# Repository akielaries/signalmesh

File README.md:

# signalmesh
*signalmesh* is a hybrid analog/digital synthesizer. For now it is a mess of reworked PCBs, perf/breadboards, and wires on my desk.

CAD work going on here right now: https://github.com/akielaries/signalmesh_CAD/

# Details
Don't forget to initialize submodules. ChibiOS is the RTOS used in this project on an STM32H7. I'm mostly building around an H755, 
occasionally the H753 but the H745/743 will probably work as well. AFAIK the only difference is the additional ARM M4 core and some
crypo acceleration stuff.

```
git submodule init
git submodule update
```

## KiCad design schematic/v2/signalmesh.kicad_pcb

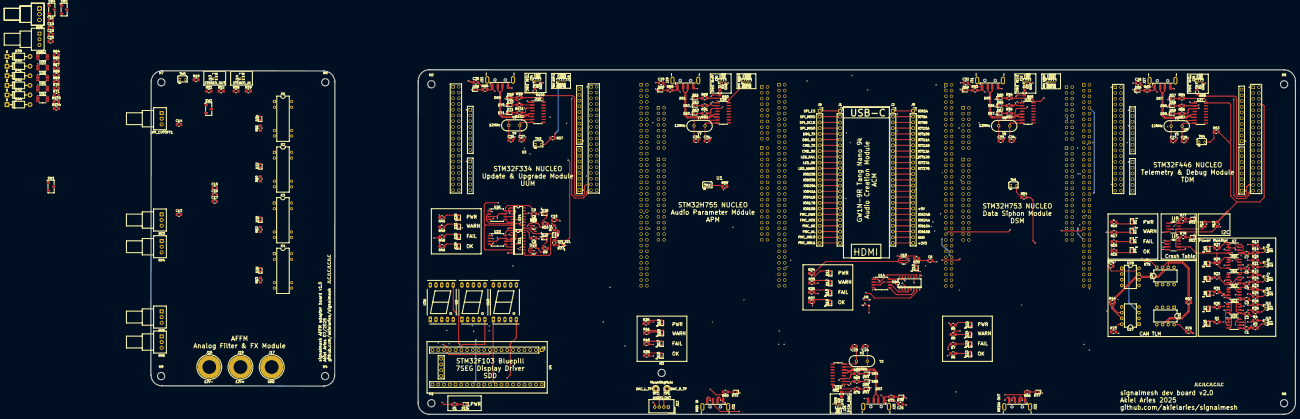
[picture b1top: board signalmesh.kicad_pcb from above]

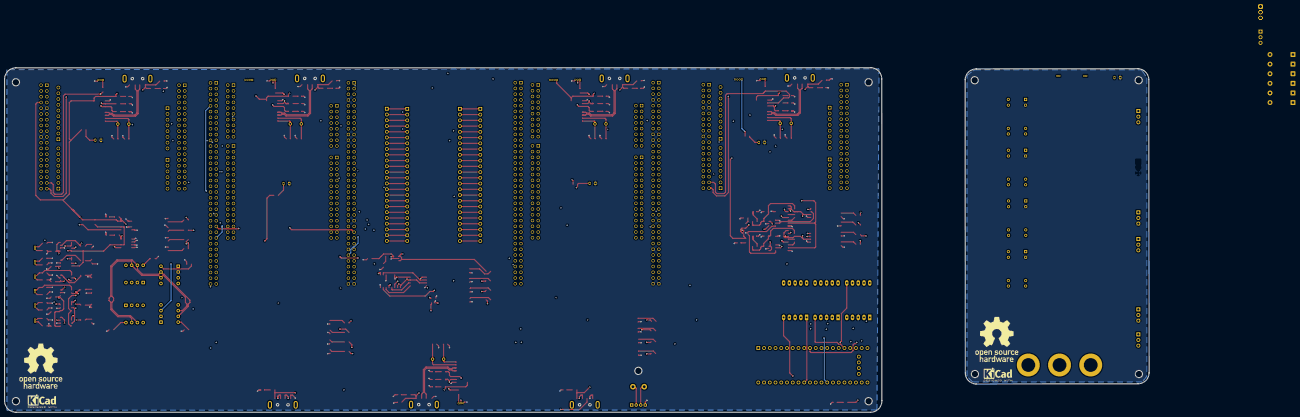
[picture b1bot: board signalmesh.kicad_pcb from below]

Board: 4 copper layers, 506.0 x 152.3 mm, 315 parts (4 on the bottom side), 286 nets.

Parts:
C1, C2, C3, C4, C5, C7, C10, C13, C14, C15, C16, C17: 0.1uf; C_0805_2012Metric
C6, C8, C9: 10uf; C_0805_2012Metric
C11, C20: 1uf; C_0805_2012Metric
C18, C19: 10nf; C_0805_2012Metric
C23, C24, C25, C26, C27, C28, C29, C30, C31, C32, C33, C34, C35, C36, C37: 22pf; C_0805_2012Metric
D1, D12, D16, D22, D29: LED_OK; LED_0603_1608Metric
D2, D13, D17, D23, D30: LED_FAIL; LED_0603_1608Metric
D3, D14, D18, D24, D31: LED_WARN; LED_0603_1608Metric
D4, D5, D6, D7, D8, D9, D10, D11, D15, D19, D20, D21, D25, D26, D28, D32, D37, D38, D51, D52, D53, D56, D57, D60, D61, D64, D65, D68, D69: LED_PWR; LED_0603_1608Metric
D27: SPI_SEL; LED_0603_1608Metric
D33: LPF_ON; LED_0603_1608Metric
D34: HPF_ON; LED_0603_1608Metric
D35: BPF_ON; LED_0603_1608Metric
D36: BSF_ON; LED_0603_1608Metric
D39, D40, D41, D42, D43, D44: 1N4001; D_DO-41_SOD81_P10.16mm_Horizontal
D54, D59, D63, D67, D71: RXD; LED_0603_1608Metric
D55, D58, D62, D66, D70: TXD; LED_0603_1608Metric
H1, H2, H3, H4, H5, H6, H7, H8, H9: MountingHole; MountingHole_3.2mm_M3
J1, J2, J8, J9: FPGA I/O; PinSocket_1x24_P2.54mm_Vertical
J3, J4, J18: LCD_display; PinHeader_1x04_P1.00mm_Horizontal
J5, J6, J7, J10, J11, J15: INA219_CONFIG; PinHeader_1x02_P1.00mm_Horizontal
J12: AUDIO_OUT; NS-Tech_Grove_1x04_P2mm_Vertical
J13: STEREO_OUT; PinHeader_1x02_P1.00mm_Vertical
J14: STEREO_IN; PinHeader_1x02_P1.00mm_Vertical
J16: 12V-; Banana_Jack_1Pin
J17: GND; Banana_Jack_1Pin
J19: 12V+; Banana_Jack_1Pin
J21, J22, J25, J27, J29, J31, J33: USB_A; USB_A_CNCTech_1001-011-01101_Horizontal
J26, J28, J30, J32, J34: UART_DEBUG; PinHeader_1x03_P1.00mm_Horizontal
K1, K2, K3, K4: DIPxx-1Axx-11x; Relay_StandexMeder_DIP_LowProfile
KiCAD_logo: KiCad-Logo2_5mm_SilkScreen
KiCAD_logo#2: KiCad-Logo2_5mm_SilkScreen
LPF_CUTOFF1: 100k; Potentiometer_Alps_RK09Y11_Single_Horizontal
OSHW: OSHW-Logo_19x20mm_SilkScreen
OSHW#2: OSHW-Logo_19x20mm_SilkScreen
R1, R2, R5, R6, R7, R8, R9, R10, R15, R16, R17, R18, R27, R29, R30, R31, R32, R33, R34, R35, R36, R37, R38, R39, R40, R41, R43, R45, R46, R48, R49, R50, R56, R60, R61, R62, R63, R72, R77, R78, R79, R80, R82, R83, R84, R86, R87, R88, R89, R91, R92, R93, R94, R96, R97, R98, R99, R101, R102: 300; R_0805_2012Metric_Pad1.20x1.40mm_HandSolder
R3, R4, R13, R14, R19, R20, R21, R22, R23, R24, R25, R26, R28, R53, R54, R55, R57, R64, R70, R73, R74, R75, R76: 10k; R_0805_2012Metric_Pad1.20x1.40mm_HandSolder
R11, R12: 4.7k; R_0805_2012Metric_Pad1.20x1.40mm_HandSolder
R42: 100; R_0805_2012Metric_Pad1.20x1.40mm_HandSolder
R44, R47: 120; R_0805_2012Metric_Pad1.20x1.40mm_HandSolder
R51, R52: 10K; R_0805_2012Metric_Pad1.20x1.40mm_HandSolder
R58, R59: 1K; R_0805_2012Metric_Pad1.20x1.40mm_HandSolder
R65, R71: 6k8; R_0805_2012Metric_Pad1.20x1.40mm_HandSolder
R67, R103: 200k; R_0805_2012Metric_Pad1.20x1.40mm_HandSolder
R68: 100k; R_0805_2012Metric_Pad1.20x1.40mm_HandSolder
R69: 33k; R_0805_2012Metric_Pad1.20x1.40mm_HandSolder
R81, R85, R90, R95, R100: 1k5; R_0805_2012Metric_Pad1.20x1.40mm_HandSolder
R104: 100K; R_0805_2012Metric_Pad1.20x1.40mm_HandSolder
RV3, RV4, RV5, RV6, RV7, RV8, RV9: 100k; Potentiometer_Alps_RK09Y11_Single_Horizontal
SW1: LPF_FBCK_OUT; Nidec_Copal_CAS-120A
SW2: LPF_IN_SW; Nidec_Copal_CAS-120A
SW4: LPF_OUT_SW; Nidec_Copal_CAS-120A
SW5: LPF_FBCK_IN; Nidec_Copal_CAS-120A
TH1, TH2, TH3, TH4, TH5: 10k; Heraeus_TO-92-2
TP1: DAC_R_TP; TestPoint_THTPad_D2.5mm_Drill1.2mm
TP2: DAC_L_TP; TestPoint_THTPad_D2.5mm_Drill1.2mm
U1, U17: NUCLEO-H753ZI; MODULE_NUCLEO-H753ZI
U2, U18, U36: SM420561N; 7SegmentLED_LTS6760_LTS6780
U3: NUCLEO-F303RE; ST_NUCLEO-F303RE
U4: YAAJ_BluePill_Part_Like; YAAJ_WeAct_BlackPill_SWD_2
U5, U8: 24LC256-I_SN; SOIC127P600X175-8N
U6: BME280; Bosch_LGA-8_2.5x2.5mm_P0.65mm_ClockwisePinNumbering
U7, U10, U11, U12, U13, U20: INA219AxD; SOIC-8_3.9x4.9mm_P1.27mm
U9: NUCLEO-F446RE; MODULE_NUCLEO-F446RE
U14, U23, U26: W25Q128JVS; SOIC-8_5.3x5.3mm_P1.27mm
U15, U22, U25: AP2112K-3.3; SOT-23-5
U16, U21, U24: 74HC4050D; SO16
U19, U37, U38, U39, U40: CH340G; SOIC-16_3.9x9.9mm_P1.27mm
U27, U29, U30, U31: MCP2551-I-P; DIP-8_W7.62mm
U28: 74LVC1G3157; SC70-6
U32, U33, U35, U41, U42: OPA196xDGK; VSSOP-8_3x3mm_P0.65mm
Y2, Y5, Y7, Y8, Y9: 12MHz; Crystal_HC49-4H_Vertical

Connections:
3V3_ACM: J2.24, J9.24, U14.3 (~WP/IO_{2}), U14.7 (~HOLD/~RESET/IO_{3}), U16.1 (VCC)
5V_7SDD: R1.2, U4.18 (5V), U20.8 (IN+)
5V_TDM: C1.2, C2.2, C3.2, C4.2, C5.2, C7.2, U7.5 (VS), U7.8 (IN+), U10.5 (VS), U11.5 (VS), U12.5 (VS), U13.5 (VS), U20.5 (VS)
/ACM/ACM_LED_FAIL: J1.9, J8.9, R37.2
/ACM/ACM_LED_OK: J1.10, J8.10, R35.2
/ACM/ACM_LED_WARN: J1.11, J8.11, R36.2
/ACM/ACM_SPI_CS: J1.1, J8.1, U16.3 (1A)
/ACM/ACM_SPI_MISO: J1.4, J8.4, U16.9 (4A)
/ACM/ACM_SPI_MOSI: J1.2, J8.2, U16.7 (3A)
/ACM/ACM_SPI_SCLK: J1.3, J8.3, U16.5 (2A)
/ACM_CMD_RX: J1.7, J8.7, U1.CN11_2 (PC11)
/ACM_CMD_TX: J1.8, J8.8, U1.CN11_1 (PC10)
/ACM_DBG_RX: J1.6, J8.6, J26.2, R82.1, U19.3 (RXD)
/ACM_DBG_TX: J1.5, J8.5, R80.1, R81.2, U19.2 (TXD)
/AFFM/AFFM_BPF_TOGGLE: K3.6, R62.1
/AFFM/AFFM_BSF_TOGGLE: K4.6, R63.1
/AFFM/AFFM_HPF_TOGGLE: K2.6, R60.1
/AFFM/AFFM_LPF_TOGGLE: K1.6, R61.1
/AFFM/AFFM_filters/BPF_IN: K3.1, K3.14, RV4.2
/AFFM/AFFM_filters/BPF_OUT: K3.7, K3.8
/AFFM/AFFM_filters/BSF_IN: K4.1, K4.14, RV5.2, RV6.2
/AFFM/AFFM_filters/BSF_OUT: K4.7, K4.8
/AFFM/AFFM_filters/HPF_IN: K2.1, K2.14
/AFFM/AFFM_filters/HPF_OUT: K2.7, K2.8
/AFFM/AFFM_filters/LPF_IN: K1.1, K1.14, SW4.2 (B)
/AFFM/AFFM_filters/LPF_OUT: K1.7, K1.8, R58.2, R59.2
/AFFM/AFFM_filters/LPFs/12V+: J19.1, U32.7 (V+), U33.7 (V+), U35.7 (V+), U41.7 (V+), U42.7 (V+)
/AFFM/AFFM_filters/LPFs/12V-: J17.1, U32.4 (V-), U33.4 (V-), U35.4 (V-), U41.4 (V-), U42.4 (V-)
/AFFM/AFFM_filters/LPFs/ACTIVE_LPF_OUT: C20.1, R103.2, SW4.3 (A)
/AFFM/AFFM_filters/LPFs/CFBACK_IN: D41.1 (K), D42.2 (A), R64.2, SW1.1 (C), SW5.3 (A), U33.3 (+), U33.6
/AFFM/AFFM_filters/LPFs/Fback_in: C20.2, R104.2, SW5.2 (B), U42.2 (-), U42.6
/AFFM/AFFM_filters/LPFs/PASSIVE_LPF_OUT: LPF_CUTOFF1.2, SW4.1 (C)
/AFFM/AFFM_filters/LPFs/RFBACK_OUT: R70.1, SW1.3 (A), SW5.1 (C), U35.3 (+), U35.6
/AFFM/AFFM_filters/MONO_IN: R51.2, R52.2, SW2.2 (B)
/APM/7SDD_CMD_RX: U1.CN11_63 (PG9), U4.6 (PA9)
/APM/7SDD_CMD_TX: U1.CN12_61 (PG14), U4.7 (PA10)
/APM/APM_I2C1_SCL: J4.3, U1.CN11_51 (PF1)
/APM/APM_I2C1_SDA: J4.2, U1.CN11_53 (PF0)
/APM/APM_LED_FAIL: R41.2, U1.CN12_34 (PC4)
/APM/APM_LED_OK: R39.2, U1.CN12_4 (PC6)
/APM/APM_LED_WARN: R40.2, U1.CN12_6 (PC5)
/APM/APM_USB_D+: J21.3 (D+), U1.CN12_14 (PA11)
/APM/APM_USB_D-: J21.2 (D-), U1.CN12_12 (PA12)
/APM_CAN_RD: U1.CN12_3 (PB8), U29.1 (TXD)
/APM_CAN_TD: U1.CN12_5 (PB9), U29.4 (RXD)
/APM_DAC_OUT_L: J12.2, J14.2, R51.1, TP1.1, U1.CN12_11 (PA5)
/APM_DAC_OUT_R: J12.3, J14.1, R52.1, TP2.1, U1.CN11_32 (PA4)
/APM_DBG_RX: J30.2, R92.1, U1.CN11_4 (PD2), U38.3 (RXD)
/APM_DBG_TX: R90.2, R91.1, U1.CN11_3 (PC12), U38.2 (TXD)
/CAN+: R44.1, R47.2, U27.7 (CAN+), U29.7 (CAN+), U30.7 (CAN+), U31.7 (CAN+)
/CAN-: R44.2, R47.1, U27.6 (CAN-), U29.6 (CAN-), U30.6 (CAN-), U31.6 (CAN-)
/DSM/DSM_I2C1_SCL: J3.3, U17.CN11_51 (PF1)
/DSM/DSM_I2C1_SDA: J3.2, U17.CN11_53 (PF0)
/DSM/DSM_LED_FAIL: R8.2, U17.CN12_34 (PC4)
/DSM/DSM_LED_OK: R6.2, U17.CN12_4 (PC6)
/DSM/DSM_LED_WARN: R7.2, U17.CN12_6 (PC5)
/DSM/DSM_USB_D+: J22.3 (D+), U17.CN12_14 (PA11)
/DSM/DSM_USB_D-: J22.2 (D-), U17.CN12_12 (PA12)
/DSM_CAN_RD: U17.CN12_3 (PB8), U30.1 (TXD)
/DSM_CAN_TD: U17.CN12_5 (PB9), U30.4 (RXD)
/DSM_DAC_IN_L: J13.1, R58.1, U17.CN12_11 (PA5)
/DSM_DAC_IN_R: J13.2, R59.1, U17.CN11_32 (PA4)
/DSM_DBG_RX: J32.2, R97.1, U17.CN11_4 (PD2), U39.3 (RXD)
/DSM_DBG_TX: R95.2, R96.1, U17.CN11_3 (PC12), U39.2 (TXD)
/FMC_CLK: J1.18, J8.18, U17.CN11_40 (PD3)
/FMC_D0: J2.1, J9.1, U17.CN12_46 (PD14)
/FMC_D1: J2.2, J9.2, U17.CN12_48 (PD15)
/FMC_D2: J2.3, J9.3, U17.CN11_57 (PD0)
/FMC_D3: J2.4, J9.4, U17.CN11_55 (PD1)
/FMC_D4: J2.5, J9.5, U17.CN12_44 (PE7)
/FMC_D5: J2.6, J9.6, U17.CN12_40 (PE8)
/FMC_D6: J2.7, J9.7, U17.CN12_52 (PE9)
/FMC_D7: J2.8, J9.8, U17.CN12_47 (PE10)
/FMC_D8: J2.9, J9.9, U17.CN12_56 (PE11)
/FMC_D9: J2.10, J9.10, U17.CN12_49 (PE12)
/FMC_D10: J2.11, J9.11, U17.CN12_55 (PE13)
/FMC_D11: J2.12, J9.12, U17.CN12_51 (PE14)
/FMC_D12: J2.13, J9.13, U17.CN12_53 (PE15)
/FMC_D13: J2.14, J9.14, U17.CN12_10 (PD8)
/FMC_D14: J2.15, J9.15, U17.CN11_69 (PD9)
/FMC_D15: J2.16, J9.16, U17.CN12_65 (PD10)
/FMC_NBL0: J1.23, J8.23, U17.CN12_64 (PE0)
/FMC_NBL1: J1.24, J8.24, U17.CN11_61 (PE1)
/FMC_NE: J1.21, J8.21, U17.CN12_19 (PC7)
/FMC_NL: J1.22, J8.22, U17.CN11_21 (PB7)
/FMC_NOE: J1.20, J8.20, U17.CN11_39 (PD4)
/FMC_NWE: J1.19, J8.19, U17.CN11_41 (PD5)
/IRQ0: U1.CN11_62 (PE6), U17.CN11_47 (PE3)
/ISR0: U1.CN11_47 (PE3), U17.CN11_62 (PE6)
/TDM/7SDD_VDD: R2.2, U20.7 (IN-)
/TDM/ACM_VDD: R29.2, U10.7 (IN-)
/TDM/APM_VDD: R30.2, U13.7 (IN-)
/TDM/DSM_VDD: R32.2, U11.7 (IN-)
/TDM/TDM_I2C1_SCL: J18.3, R11.1, U5.6 (SCL), U6.4 (SCK), U7.4 (SCL), U8.6 (SCL), U9.CN10_3 (PB8), U10.4 (SCL), U11.4 (SCL), U12.4 (SCL), U13.4 (SCL), U20.4 (SCL)
/TDM/TDM_I2C1_SDA: J18.2, R12.1, U5.5 (SDA), U6.5 (SDO), U7.3 (SDA), U8.5 (SDA), U9.CN10_5 (PB9), U10.3 (SDA), U11.3 (SDA), U12.3 (SDA), U13.3 (SDA), U20.3 (SDA)
/TDM/TDM_LED_FAIL: R18.2, U9.CN10_6 (PC5)
/TDM/TDM_LED_OK: R16.2, U9.CN10_11 (PA5)
/TDM/TDM_LED_WARN: R17.2, U9.CN10_34 (PC4)
/TDM/UUM_VDD: R31.2, U12.7 (IN-)
/TDM_CAN_RD: U9.CN10_14 (PA11), U31.1 (TXD)
/TDM_CAN_TD: U9.CN10_12 (PA12), U31.4 (RXD)
/TDM_DBG_RX: J28.2, R87.1, U9.CN10_37 (PA3), U37.3 (RXD)
/TDM_DBG_TX: R85.2, R86.1, U9.CN10_35 (PA2), U37.2 (TXD)
/USB_debug_ACM/D+: J25.3 (D+), U19.5 (UD+)
/USB_debug_ACM/D-: J25.2 (D-), U19.6 (UD-)
/USB_debug_ACM/DBG_TX: J26.1, R81.1
/USB_debug_APM/D+: J29.3 (D+), U38.5 (UD+)
/USB_debug_APM/D-: J29.2 (D-), U38.6 (UD-)
/USB_debug_APM/DBG_TX: J30.1, R90.1
/USB_debug_DSM/D+: J31.3 (D+), U39.5 (UD+)
/USB_debug_DSM/D-: J31.2 (D-), U39.6 (UD-)
/USB_debug_DSM/DBG_TX: J32.1, R95.1
/USB_debug_TDM/D+: J27.3 (D+), U37.5 (UD+)
/USB_debug_TDM/D-: J27.2 (D-), U37.6 (UD-)
/USB_debug_TDM/DBG_TX: J28.1, R85.1
/USB_debug_UUM/D+: J33.3 (D+), U40.5 (UD+)
/USB_debug_UUM/D-: J33.2 (D-), U40.6 (UD-)
/USB_debug_UUM/DBG_TX: J34.1, R100.1
/UUM/UUM_LED_FAIL: R49.2, U3.CN7_38 (PC0)
/UUM/UUM_LED_OK: R46.2, U3.CN7_35 (PC2)
/UUM/UUM_LED_WARN: R48.2, U3.CN7_36 (PC1)
/UUM/UUM_SPI1_CS: U3.CN10_23 (PA8), U21.3 (1A)
/UUM/UUM_SPI1_MISO: U3.CN10_13 (PA6), U28.6
/UUM/UUM_SPI1_MOSI: U3.CN10_15 (PA7), U21.7 (3A), U24.7 (3A)
/UUM/UUM_SPI1_SCLK: U3.CN10_11 (PA5), U21.5 (2A), U24.5 (2A)
/UUM/UUM_SPI2_CS: U3.CN10_21 (PA9), U24.3 (1A)
/UUM/UUM_SPI_SEL: R43.1, U3.CN7_25 (PC14), U28.4
/UUM/UUM_spiflash/UUM_SPI1_MISO_A: U21.9 (4A), U28.3
/UUM/UUM_spiflash/UUM_SPI1_MISO_B: U24.9 (4A), U28.1
/UUM_CAN_RD: U3.CN10_3 (PB8), U27.1 (TXD)
/UUM_CAN_TD: U3.CN10_5 (PB9), U27.4 (RXD)
/UUM_DBG_RX: J34.2, R102.1, U3.CN10_37 (PA3), U40.3 (RXD)
/UUM_DBG_TX: R100.2, R101.1, U3.CN10_35 (PA2), U40.2 (TXD)
ACM_VDD: C25.2, J2.18, J9.18, J25.1 (VBUS), R34.2, R72.2, R79.2, U15.1 (VIN), U15.3 (EN), U19.16 (VCC)
APM_VDD: C29.2, J4.1, J21.1 (VBUS), J29.1 (VBUS), R38.2, R50.2, R88.2, R89.2, U1.CN11_18 (5V), U29.3 (VDD), U38.16 (VCC)
DSM_VDD: C32.2, J3.1, J22.1 (VBUS), J31.1 (VBUS), R5.2, R56.2, R93.2, R94.2, U17.CN11_18 (5V), U30.3 (VDD), U39.16 (VCC)
GND: C1.1, C2.1, C3.1, C4.1, C5.1, C6.2, C7.1, C8.2, C9.2, C10.2, C14.1, C15.1, C17.1, C19.2, C23.2, C24.2, C25.1, C26.1, C27.2, C28.2, C29.1, C30.2, C31.2, C32.1, C33.2, C34.2, C35.1, C36.2, C37.2, D1.1 (K), D2.1 (K), D3.1 (K), D4.1 (K), D5.1 (K), D6.1 (K), D7.1 (K), D8.1 (K), D9.1 (K), D10.1 (K), D11.1 (K), D12.1 (K), D13.1 (K), D14.1 (K), D15.1 (K), D16.1 (K), D17.1 (K), D18.1 (K), D19.1 (K), D20.1 (K), D21.1 (K), D22.1 (K), D23.1 (K), D24.1 (K), D25.1 (K), D26.1 (K), D27.1 (K), D28.1 (K), D29.1 (K), D30.1 (K), D31.1 (K), D32.1 (K), D33.1 (K), D34.1 (K), D35.1 (K), D36.1 (K), D37.1 (K), D38.1 (K), D51.1 (K), D52.1 (K), D53.1 (K), D54.1 (K), D55.1 (K), D56.1 (K), D57.1 (K), D58.1 (K), D59.1 (K), D60.1 (K), D61.1 (K), D62.1 (K), D63.1 (K), D64.1 (K), D65.1 (K), D66.1 (K), D67.1 (K), D68.1 (K), D69.1 (K), D70.1 (K), D71.1 (K), J2.23, J3.4, J4.4, J9.23, J12.4, J18.4, J21.4 (GND), J22.4 (GND), J25.4 (GND), J26.3, J27.4 (GND), J28.3, J29.4 (GND), J30.3, J31.4 (GND), J32.3, J33.4 (GND), J34.3, K1.2, K2.2, K3.2, K4.2, R3.1, R4.1, R13.1, R14.1, R20.1, R21.1, R22.1, R23.1, R24.1, R25.1, R26.1, R28.1, R65.1, R67.1, R69.1, R71.1, R73.2, R74.2, R75.2, R76.2, R103.1, R104.1, RV3.3, RV5.3, TH1.1, TH2.1, TH3.1, TH4.1, TH5.1, U1.CN11_8 (GND_CN11), U1.CN11_19 (GND_CN11), U1.CN11_20 (GND_CN11), U1.CN11_22 (GND_CN11), U1.CN11_49 (GND_CN11), U1.CN11_60 (GND_CN11), U1.CN11_71 (GND_CN11), U1.CN11_72 (GND_CN11), U2.3 (CC), U2.8 (CC), U3.CN10_9 (GND_S2), U3.CN10_20 (GND_S2), U4.39 (GND), U5.1 (A0), U5.2 (A1), U5.3 (A2), U5.4 (VSS), U6.1 (GND), U6.7 (GND), U7.6 (GND), U8.1 (A0), U8.3 (A2), U8.4 (VSS), U9.CN10_9 (CN10_GND), U9.CN10_20 (CN10_GND), U10.6 (GND), U11.6 (GND), U12.6 (GND), U13.6 (GND), U14.4 (GND), U15.2 (GND), U16.8 (GND), U16.11 (5A), U16.14 (6A), U17.CN11_8 (GND_CN11), U17.CN11_19 (GND_CN11), U17.CN11_20 (GND_CN11), U17.CN11_22 (GND_CN11), U17.CN11_49 (GND_CN11), U17.CN11_60 (GND_CN11), U17.CN11_71 (GND_CN11), U17.CN11_72 (GND_CN11), U18.3 (CC), U18.8 (CC), U19.1 (GND), U20.6 (GND), U21.8 (GND), U21.11 (5A), U21.14 (6A), U22.2 (GND), U23.4 (GND), U24.8 (GND), U24.11 (5A), U24.14 (6A), U25.2 (GND), U26.4 (GND), U27.2 (VSS), U28.2 (GND), U29.2 (VSS), U30.2 (VSS), U31.2 (VSS), U36.3 (CC), U36.8 (CC), U37.1 (GND), U38.1 (GND), U39.1 (GND), U40.1 (GND)
unnamed: C10.1, R42.2
unnamed: C11.1, R67.2, R68.2, RV9.1
unnamed: C13.1, RV3.1
unnamed: C14.2, LPF_CUTOFF1.3
unnamed: C15.2, RV4.3
unnamed: C16.1, RV5.1
unnamed: C16.2, RV6.1
unnamed: C17.2, RV6.3
unnamed: D1.2 (A), R16.1
unnamed: D2.2 (A), R17.1
unnamed: D3.2 (A), R18.1
unnamed: D4.2 (A), R15.1
unnamed: D5.2 (A), R27.1
unnamed: D6.2 (A), R29.1
unnamed: D7.2 (A), R30.1
unnamed: D8.2 (A), R31.1
unnamed: D9.2 (A), R32.1
unnamed: D10.2 (A), R33.2
unnamed: D11.2 (A), R34.1
unnamed: D12.2 (A), R35.1
unnamed: D13.2 (A), R36.1
unnamed: D14.2 (A), R37.1
unnamed: D15.2 (A), R38.1
unnamed: D16.2 (A), R39.1
unnamed: D17.2 (A), R40.1
unnamed: D18.2 (A), R41.1
unnamed: D19.2 (A), R1.1
unnamed: D20.2 (A), R2.1
unnamed: D21.2 (A), R5.1
unnamed: D22.2 (A), R6.1
unnamed: D23.2 (A), R7.1
unnamed: D24.2 (A), R8.1
unnamed: D25.2 (A), R9.2
unnamed: D26.2 (A), R10.2
unnamed: D27.2 (A), R43.2
unnamed: D28.2 (A), R45.1
unnamed: D29.2 (A), R46.1
unnamed: D30.2 (A), R48.1
unnamed: D31.2 (A), R49.1
unnamed: D32.2 (A), R50.1
unnamed: D33.2 (A), R61.2
unnamed: D34.2 (A), R60.2
unnamed: D35.2 (A), R62.2
unnamed: D36.2 (A), R63.2
unnamed: D37.2 (A), R56.1
unnamed: D38.2 (A), R72.1
unnamed: D39.2 (A), D44.1 (K), R64.1, R65.2, U33.2 (-)
unnamed: D39.1 (K), D40.2 (A)
unnamed: D40.1 (K), D41.2 (A)
unnamed: D42.1 (K), D43.2 (A)
unnamed: D43.1 (K), D44.2 (A)
unnamed: D51.2 (A), R77.2
unnamed: D52.2 (A), R78.2
unnamed: D53.2 (A), R79.1
unnamed: D54.2 (A), R82.2
unnamed: D55.2 (A), R80.2
unnamed: D56.2 (A), R83.1
unnamed: D57.2 (A), R84.1
unnamed: D58.2 (A), R86.2
unnamed: D59.2 (A), R87.2
unnamed: D60.2 (A), R88.1
unnamed: D61.2 (A), R89.1
unnamed: D62.2 (A), R91.2
unnamed: D63.2 (A), R92.2
unnamed: D64.2 (A), R93.1
unnamed: D65.2 (A), R94.1
unnamed: D66.2 (A), R96.2
unnamed: D67.2 (A), R97.2
unnamed: D68.2 (A), R98.1
unnamed: D69.2 (A), R99.1
unnamed: D70.2 (A), R101.2
unnamed: D71.2 (A), R102.2
unnamed: J5.1, J5.2, R13.2, R14.2, U7.1 (A1), U7.2 (A0)
unnamed: J6.1, J6.2, R20.2, R21.2, U10.1 (A1), U10.2 (A0)
unnamed: J7.1, J7.2, R22.2, R24.2, U11.1 (A1), U11.2 (A0)
unnamed: J10.1, J10.2, R23.2, R25.2, U12.1 (A1), U12.2 (A0)
unnamed: J11.1, J11.2, R26.2, R28.2, U13.1 (A1), U13.2 (A0)
unnamed: J15.1, J15.2, R3.2, R4.2, U20.1 (A1), U20.2 (A0)
unnamed: R19.1, TH5.2
unnamed: RV3.2, RV4.1
unnamed: C18.2, SW1.2 (B)
unnamed: LPF_CUTOFF1.1, SW2.3 (A)
unnamed: C11.2, SW2.1 (C)
unnamed: U2.7 (A), U4.28 (PA3)
unnamed: U2.6 (B), U4.27 (PA2)
unnamed: U2.4 (C), U4.26 (PA1)
unnamed: U2.2 (D), U4.25 (PA0)
unnamed: U2.5 (DP), U4.16 (PB8)
unnamed: U2.1 (E), U4.24 (PC15)
unnamed: U2.9 (F), U4.23 (PC14)
unnamed: U2.10 (G), U4.17 (PB9)
unnamed: R57.1, TH3.2, U9.CN7_32 (PA4)
unnamed: R55.1, TH2.2, U9.CN7_34 (PB0)
unnamed: R54.1, TH1.2, U9.CN7_38 (PC0/PB8)
unnamed: R53.1, TH4.2, U9.CN7_36 (PC1/PB9)
unnamed: U14.6 (CLK), U16.4 (2Y)
unnamed: U14.5 (DI/IO_{0}), U16.6 (3Y)
unnamed: U14.2 (DO/IO_{1}), U16.10 (4Y)
unnamed: C6.1, R33.1, U14.8 (VCC), U15.5 (VOUT)
unnamed: U14.1 (~CS), U16.2 (1Y)
unnamed: U4.36 (PB11), U18.7 (A)
unnamed: U4.35 (PB10), U18.6 (B)
unnamed: U4.34 (PB1), U18.4 (C)
unnamed: U4.33 (PB0), U18.2 (D)
unnamed: U4.29 (PA4), U18.5 (DP)
unnamed: U4.32 (PA7), U18.1 (E)
unnamed: U4.31 (PA6), U18.9 (F)
unnamed: U4.30 (PA5), U18.10 (G)
unnamed: C24.1, U19.7 (XI), Y2.1
unnamed: C23.1, U19.8 (XO), Y2.2
unnamed: U21.2 (1Y), U23.1 (~CS)
unnamed: U21.4 (2Y), U23.6 (CLK)
unnamed: U21.6 (3Y), U23.5 (DI/IO_{0})
unnamed: U21.10 (4Y), U23.2 (DO/IO_{1})
unnamed: C8.1, R9.1, U22.5 (VOUT), U23.8 (VCC)
unnamed: U24.2 (1Y), U26.1 (~CS)
unnamed: U24.4 (2Y), U26.6 (CLK)
unnamed: U24.6 (3Y), U26.5 (DI/IO_{0})
unnamed: U24.10 (4Y), U26.2 (DO/IO_{1})
unnamed: C9.1, R10.1, U25.5 (VOUT), U26.8 (VCC)
unnamed: R73.1, U27.8 (Rs)
unnamed: R74.1, U29.8 (Rs)
unnamed: R75.1, U30.8 (Rs)
unnamed: R76.1, U31.8 (Rs)
unnamed: R68.1, R69.2, RV9.3, U32.3 (+)
unnamed: RV7.1, U32.2 (-), U32.6
unnamed: R70.2, R71.2, U35.2 (-)
unnamed: U4.15 (PB7), U36.7 (A)
unnamed: U4.14 (PB6), U36.6 (B)
unnamed: U4.13 (PB5), U36.4 (C)
unnamed: U4.12 (PB4), U36.2 (D)
unnamed: U4.8 (PA11), U36.5 (DP)
unnamed: U4.11 (PB3), U36.1 (E)
unnamed: U4.10 (PA15), U36.9 (F)
unnamed: U4.9 (PA12), U36.10 (G)
unnamed: C27.1, U37.7 (XI), Y5.1
unnamed: C28.1, U37.8 (XO), Y5.2
unnamed: C30.1, U38.7 (XI), Y7.1
unnamed: C31.1, U38.8 (XO), Y7.2
unnamed: C33.1, U39.7 (XI), Y8.1
unnamed: C34.1, U39.8 (XO), Y8.2
unnamed: C36.1, U40.7 (XI), Y9.1
unnamed: C37.1, U40.8 (XO), Y9.2
unnamed: C18.1, RV7.3, U41.3 (+)
unnamed: RV8.1, U41.2 (-), U41.6
unnamed: C19.1, RV8.3, U42.3 (+)
TDM_VDD: C26.2, J18.1, J27.1 (VBUS), R11.2, R12.2, R15.2, R19.2, R27.2, R53.2, R54.2, R55.2, R57.2, R77.1, R78.1, R83.2, R84.2, U5.8 (VCC), U6.8 (VDD), U7.7 (IN-), U8.8 (VCC), U9.CN10_8 (U5V), U31.3 (VDD), U37.16 (VCC)
UUM_3v3: R42.1, U3.CN7_16 (+3V3_S1), U21.1 (VCC), U23.3 (~WP/IO_{2}), U23.7 (~HOLD/~RESET/IO_{3}), U24.1 (VCC), U26.3 (~WP/IO_{2}), U26.7 (~HOLD/~RESET/IO_{3}), U28.5 (VCC)
UUM_VDD: C35.2, J33.1 (VBUS), R45.2, R98.2, R99.2, U3.CN7_18 (+5V_S1), U22.1 (VIN), U22.3 (EN), U25.1 (VIN), U25.3 (EN), U27.3 (VDD), U40.16 (VCC)

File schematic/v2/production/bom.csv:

Designator,Footprint,Quantity,Value,LCSC Part #
"C1, C10, C2, C3, C4, C5, C7",0805,7,0.1uf,
"C11, C12, C13, C14, C15, C16, C17, C18, C19, C20, C21, C22, C23, C24, C25",0805,15,22pf,
"C6, C8, C9",0805,3,10uf,
"D1, D12, D16, D22, D29",0603,5,LED_OK,
"D10, D11, D15, D19, D20, D21, D25, D26, D27, D28, D32, D33, D34, D37, D38, D39, D4, D40, D42, D43, D46, D47, D5, D51, D52, D53, D6, D7, D8, D9",0603,30,LED_PWR,
"D13, D17, D2, D23, D30",0603,5,LED_FAIL,
"D14, D18, D24, D3, D31",0603,5,LED_WARN,
"D35, D41, D44, D48, D55",0603,5,TXD,
"D36, D45, D49, D50, D54",0603,5,RXD,
"J1, J2, J8, J9",PinSocket_1x24_P2.54mm_Vertical,4,FPGA I/O,
"J10, J11, J15, J5, J6, J7",PinHeader_1x02_P1.00mm_Horizontal,6,INA219_CONFIG,
"J12, J16, J21, J22, J23, J24, J25",USB_A_CNCTech_1001-011-01101_Horizontal,7,USB_A,
J13,PinHeader_1x03_P1.00mm_Horizontal,1,UUM_DBG,
J14,PinHeader_1x03_P1.00mm_Horizontal,1,ACM_DBG,
"J17, J18, J3",PinHeader_1x04_P1.00mm_Vertical_SMD_Pin1Left,3,LCD_display,
J19,Jack_3.5mm_CUI_SJ-3523-SMT_Horizontal,1,AudioJack3,
J20,PinHeader_1x03_P1.00mm_Horizontal,1,DSM_DBG,
J26,PinHeader_1x03_P1.00mm_Horizontal,1,APM_DBG,
J4,PinHeader_1x03_P1.00mm_Horizontal,1,TDM_DBG,
"R1, R10, R15, R16, R17, R18, R2, R27, R29, R30, R31, R32, R33, R34, R35, R36, R37, R38, R39, R40, R41, R43, R45, R46, R48, R49, R5, R50, R51, R52, R53, R54, R56, R57, R58, R6, R60, R61, R62, R63, R64, R65, R67, R68, R69, R7, R70, R72, R77, R78, R79, R8, R80, R82, R9",0805,55,300,
"R11, R12",0805,2,4.7k,
"R13, R14, R19, R20, R21, R22, R23, R24, R25, R26, R28, R3, R4, R73, R74, R75, R76",0805,17,10k,
R42,0805,1,100,
"R44, R47",0805,2,120,
"R55, R59, R66, R71, R81",0805,5,1k5,
TH1,R_LDR_4.9x4.2mm_P2.54mm_Vertical,1,10k,
"U1, U17",MODULE_NUCLEO-H753ZI,2,NUCLEO-H753ZI,
"U10, U11, U12, U13, U20, U7",SOIC-8_3.9x4.9mm_P1.27mm,6,INA219AxD,
"U14, U23, U26",SOIC-8_5.3x5.3mm_P1.27mm,3,W25Q128JVS,
"U15, U22, U25",SOT-23-5,3,AP2112K-3.3,
"U16, U21, U24",SO16,3,74HC4050D,
"U18, U2, U36",7SegmentLED_LTS6760_LTS6780,3,SM420561N,
"U19, U32, U33, U34, U35",SOIC-16_3.9x9.9mm_P1.27mm,5,CH340G,
"U27, U29, U30, U31",DIP-8_W7.62mm,4,MCP2551-I-P,
U28,SC70-6,1,74LVC1G3157,
U3,ST_NUCLEO-F303RE,1,NUCLEO-F303RE,
U4,YAAJ_WeAct_BlackPill_SWD_2,1,YAAJ_BluePill_Part_Like,
"U5, U8",SOIC127P600X175-8N,2,24LC256-I_SN,24LC256-I/SN
U6,Bosch_LGA-8_2.5x2.5mm_P0.65mm_ClockwisePinNumbering,1,BME280,
U9,MODULE_NUCLEO-F446RE,1,NUCLEO-F446RE,
"Y1, Y2",Crystal_HC49-4H_Vertical,2,12MHz,
"Y3, Y4, Y6",Crystal_C26-LF_D2.1mm_L6.5mm_Horizontal,3,12MHz,

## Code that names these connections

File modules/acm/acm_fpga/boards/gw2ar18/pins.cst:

// 27 MHz system clock (bank 7)
IO_LOC  "HCLK" 4;
IO_PORT "HCLK" PULL_MODE=NONE;

// S1 reset button (active high; board has external 1k pull-down R6)
IO_LOC  "HRST" 88;
IO_PORT "HRST" IO_TYPE=LVCMOS33 PULL_MODE=NONE;

// fabric heartbeat UART TX, FPGA pin 73 (IOT40A)
IO_LOC  "UART_TX" 73;
IO_PORT "UART_TX" IO_TYPE=LVCMOS33 PULL_MODE=NONE DRIVE=8;

// 6 user leds (bank 6)
IO_LOC  "LED[5]" 20;
IO_PORT "LED[5]" IO_TYPE=LVCMOS33 PULL_MODE=NONE DRIVE=8;
IO_LOC  "LED[4]" 19;
IO_PORT "LED[4]" IO_TYPE=LVCMOS33 PULL_MODE=NONE DRIVE=8;
IO_LOC  "LED[3]" 18;
IO_PORT "LED[3]" IO_TYPE=LVCMOS33 PULL_MODE=NONE DRIVE=8;
IO_LOC  "LED[2]" 17;
IO_PORT "LED[2]" IO_TYPE=LVCMOS33 PULL_MODE=NONE DRIVE=8;
IO_LOC  "LED[1]" 16;
IO_PORT "LED[1]" IO_TYPE=LVCMOS33 PULL_MODE=NONE DRIVE=8;
IO_LOC  "LED[0]" 15;
IO_PORT "LED[0]" IO_TYPE=LVCMOS33 PULL_MODE=NONE DRIVE=8;

// ===========================================================================
// FMC multiplexed bus to the STM32 (16-bit AD + control), all LVCMOS33.
// AD is bidirectional; NADV/NOE/NWE/NE1 are inputs (pulled up so they idle
// deasserted before the STM32 brings FMC up); NWAIT is an output.
// fpga pin <-- jumper --> STM32 pin. run the bus slow for the breadboard PoC.
// ===========================================================================

// AD bus (16-bit: D0..D15)
IO_LOC  "FMC_AD[0]"  76;   // STM32 PD14
IO_PORT "FMC_AD[0]"  IO_TYPE=LVCMOS33 PULL_MODE=NONE;
IO_LOC  "FMC_AD[1]"  80;   // STM32 PD15
IO_PORT "FMC_AD[1]"  IO_TYPE=LVCMOS33 PULL_MODE=NONE;
IO_LOC  "FMC_AD[2]"  42;   // STM32 PD0
IO_PORT "FMC_AD[2]"  IO_TYPE=LVCMOS33 PULL_MODE=NONE;
IO_LOC  "FMC_AD[3]"  41;   // STM32 PD1
IO_PORT "FMC_AD[3]"  IO_TYPE=LVCMOS33 PULL_MODE=NONE;
IO_LOC  "FMC_AD[4]"  56;   // STM32 PE7
IO_PORT "FMC_AD[4]"  IO_TYPE=LVCMOS33 PULL_MODE=NONE;
IO_LOC  "FMC_AD[5]"  54;   // STM32 PE8
IO_PORT "FMC_AD[5]"  IO_TYPE=LVCMOS33 PULL_MODE=NONE;
IO_LOC  "FMC_AD[6]"  51;   // STM32 PE9
IO_PORT "FMC_AD[6]"  IO_TYPE=LVCMOS33 PULL_MODE=NONE;
IO_LOC  "FMC_AD[7]"  48;   // STM32 PE10
IO_PORT "FMC_AD[7]"  IO_TYPE=LVCMOS33 PULL_MODE=NONE;
IO_LOC  "FMC_AD[8]"  55;   // STM32 PE11
IO_PORT "FMC_AD[8]"  IO_TYPE=LVCMOS33 PULL_MODE=NONE;
IO_LOC  "FMC_AD[9]"  49;   // STM32 PE12
IO_PORT "FMC_AD[9]"  IO_TYPE=LVCMOS33 PULL_MODE=NONE;
IO_LOC  "FMC_AD[10]" 86;   // STM32 PE13
IO_PORT "FMC_AD[10]" IO_TYPE=LVCMOS33 PULL_MODE=NONE;
IO_LOC  "FMC_AD[11]" 79;   // STM32 PE14
IO_PORT "FMC_AD[11]" IO_TYPE=LVCMOS33 PULL_MODE=NONE;
IO_LOC  "FMC_AD[12]" 72;   // STM32 PE15
IO_PORT "FMC_AD[12]" IO_TYPE=LVCMOS33 PULL_MODE=NONE;
IO_LOC  "FMC_AD[13]" 71;   // STM32 PD8
IO_PORT "FMC_AD[13]" IO_TYPE=LVCMOS33 PULL_MODE=NONE;
IO_LOC  "FMC_AD[14]" 53;   // STM32 PD9 -- WAS BAD on 53/74/75, pick a clean pin
IO_PORT "FMC_AD[14]" IO_TYPE=LVCMOS33 PULL_MODE=NONE;
IO_LOC  "FMC_AD[15]" 52;   // STM32 PD10
IO_PORT "FMC_AD[15]" IO_TYPE=LVCMOS33 PULL_MODE=NONE;

// control
IO_LOC  "FMC_NADV"  31;    // STM32 PB7 (NL)
IO_PORT "FMC_NADV"  IO_TYPE=LVCMOS33 PULL_MODE=UP;
IO_LOC  "FMC_NOE"   26;    // STM32 PD4
IO_PORT "FMC_NOE"   IO_TYPE=LVCMOS33 PULL_MODE=UP;
IO_LOC  "FMC_NWE"   25;    // STM32 PD5
IO_PORT "FMC_NWE"   IO_TYPE=LVCMOS33 PULL_MODE=UP;
IO_LOC  "FMC_NE1"   29;    // STM32 PC7
IO_PORT "FMC_NE1"   IO_TYPE=LVCMOS33 PULL_MODE=UP;
IO_LOC  "FMC_NWAIT" 30;    // STM32 PC6
IO_PORT "FMC_NWAIT" IO_TYPE=LVCMOS33 PULL_MODE=NONE DRIVE=8;

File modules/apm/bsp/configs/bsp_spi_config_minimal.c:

#include "bsp_spi_config.h"
#include "hal.h"

// SPI1 configuration for W25Q64
// SCK: PA5, MISO: PA6, MOSI: PA7
// CS: PA4 (software controlled)

static const SPIConfig spi1_cfg = {
  .circular = FALSE,
  .end_cb   = NULL,
  .ssport   = 0, // CS managed manually
  .sspad    = 0,
  // STM32H7 uses CFG1/CFG2 registers - using raw values
  .cfg1 = 0x40000007, // PCLK/32, 8-bit data
  .cfg2 = 0x00400000  // Master mode, full duplex
};

// Global SPI bus configuration for SPI1
spi_bus_t spi1_bus_config = {
  .spi_driver = 0, // SPID1 (will be fixed after compilation)
  .spi_config = 0, // &spi1_cfg (will be fixed after compilation)
  .cs_port    = 0, // GPIOA (will be fixed after compilation)
  .cs_pin     = 4,
};

void bsp_spi_init(void) {
  // This will be implemented after getting compilation working
  // Configure SPI1 GPIO pins
  // Start SPI1 driver
}

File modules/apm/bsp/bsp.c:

#include <stddef.h>

#include "hal.h"
#include "ch.h"

#include "bsp/bsp.h"

#include "bsp/utils/bsp_gpt.h"
#include "bsp/utils/bsp_io.h"

#include "bsp/configs/bsp_uart_config.h"
#include "bsp/configs/bsp_i2c_config.h"
#include "bsp/configs/bsp_spi_config.h"

#include "drivers/driver_registry.h"
#include "drivers/driver_api.h"

#include "drivers/ina219.h"
#include "drivers/ina3221.h"
#include "drivers/bme280.h"
#include "drivers/bh1750.h"
#include "drivers/aht2x.h"
#include "drivers/24lc256.h"
#include "drivers/w25qxx.h"
#include "drivers/servo.h"
#include "drivers/gm009605.h"
#include "drivers/lcd2004.h"

#include "version_gen.h" // generated: FW_VERSION_STRING etc.



// private data for ina219
static ina219_t ina219_dev_data[2];
// private data for ina3221
static ina3221_t ina3221_dev_data;
// private data for bme280
// static bme280_t bme280_dev_data; // BME280 driver doesn't have a private data struct
// private data for bh1750
static bh1750_t bh1750_dev_data;
static aht2x_t aht2x_dev_data;
static eeprom_24lc256_t eeprom_24lc256_dev_data;
// private data for w25qxx
static w25qxx_t w25qxx_dev_data_1;
static w25qxx_t w25qxx_dev_data_2;
// private data for servo
// static servo_t servo_dev_data; // servo driver doesn't have a private data struct
// private data for gm009605
static gm009605_t gm009605_dev_data;
static lcd2004_t lcd2004_dev_data;


// array of devices present on APM
device_t board_devices[] = {
    {
        .name = "ina219_main",
        .driver = &ina219_driver,
        .bus = &I2CD1,
        .addr = 0x40,
        .priv = &ina219_dev_data[0],
        .is_active = true
    },
    {
        .name = "ina219_aux",
        .driver = &ina219_driver,
        .bus = &I2CD1,
        .addr = 0x45, // A0 and A1 pins grounded
        .priv = &ina219_dev_data[1],
        .is_active = true
    },
    {
        .name = "ina3221",
        .driver = &ina3221_driver,
        .bus = &I2CD1,
        .addr = 0x40, // Note: This may conflict with ina219_main
        .priv = &ina3221_dev_data,
        .is_active = false
    },
    {
        .name = "aht2x",
        .driver = &aht2x_driver,
        .bus = &I2CD1,
        .addr = 0x38,
        .priv = &aht2x_dev_data,
        .is_active = false
    },
    {
        .name = "bme280",
        .driver = &bme280_driver,
        .bus = &I2CD1,
        .addr = 0x76,
        .priv = NULL,
        .is_active = false
    },
    {
        .name = "bh1750",
        .driver = &bh1750_driver,
        .bus = &I2CD1,
        .addr = 0x23,
        .priv = &bh1750_dev_data,
        .is_active = false
    },
    {
        .name = "24lc256",
        .driver = &eeprom_24lc256_driver,
        .bus = &I2CD1,
        .addr = 0x50,
        .priv = &eeprom_24lc256_dev_data,
        .is_active = false
    },
    {
        .name = "w25qxx_1",
        .driver = &w25qxx_driver,
        .bus = &spi_bus_w25qxx_1,
        .addr = 0, // SPI uses CS pin, not address
        .priv = &w25qxx_dev_data_1,
        .is_active = false
    },
    {
        .name = "w25qxx_2",
        .driver = &w25qxx_driver,
        .bus = &spi_bus_w25qxx_2,
        .addr = 0, // SPI uses CS pin, not address
        .priv = &w25qxx_dev_data_2,
        .is_active = false
    },
    {
        .name = "gm009605",
        .driver = &gm009605_driver,
        .bus = &I2CD1,
        .addr = 0x3C,
        .priv = &gm009605_dev_data,
        .is_active = true
    },
    {
        .name = "lcd2004",
        .driver = &lcd2004_driver,
        .bus = &I2CD1,
        .addr = 0x26,          // PCF8574 backpack on this module lands at 0x26 (not the 0x27 default)
        .priv = &lcd2004_dev_data,
        .is_active = true
    },
    /*
    {
        .name = "servo",
        .driver = &servo_driver,
        .bus = NULL,
        .priv = NULL,
        .is_active = false
    },
    */
};


// number of devices on APM
const size_t num_board_devices = sizeof(board_devices) / sizeof(board_devices[0]);


// onboard-LED heartbeat: a low-priority "is it alive" sweep over the three
// nucleo user LEDs. started by bsp_init, not from app main
static const ioline_t heartbeat_leds[] = {
  LINE_LED_GREEN,
  LINE_LED_YELLOW,
  LINE_LED_RED,
};

static THD_WORKING_AREA(wa_heartbeat, 256);
static THD_FUNCTION(heartbeat_thread, arg) {
  (void)arg;
  chRegSetThreadName("heartbeat");

  const size_t n = sizeof(heartbeat_leds) / sizeof(heartbeat_leds[0]);
  for (size_t i = 0; i < n; i++) {
    palSetLineMode(heartbeat_leds[i], PAL_MODE_OUTPUT_PUSHPULL);
    palClearLine(heartbeat_leds[i]);
  }

  // sweep one LED at a time so the cycle shows the scheduler is alive
  size_t cur = 0;
  while (true) {
    palSetLine(heartbeat_leds[cur]);
    chThdSleepMilliseconds(500);
    palClearLine(heartbeat_leds[cur]);
    cur = (cur + 1U) % n;
  }
}

static void heartbeat_start(void) {
  chThdCreateStatic(wa_heartbeat, sizeof(wa_heartbeat),
                    LOWPRIO, heartbeat_thread, NULL);
}


void bsp_init(void) {
  halInit();
  chSysInit();

  // initialize debug UART
  bsp_io_init();

  bsp_printf("\n...Starting...\n\n");
  bsp_printf("%s\n", FW_VERSION_STRING); // e.g. APM v1.0.0-7e98556-dirty

  bsp_printf("booting...");
  for (uint8_t i = 0; i < 3; i++) {
    bsp_printf(".");
    chThdSleepMilliseconds(250);
  }
  bsp_printf("\n");

  // chip info
  bsp_printf("System tick freq: %u Hz\n", CH_CFG_ST_FREQUENCY);
  bsp_printf("DBGMCU->IDCODE: 0x%08lX\r\n", DBGMCU->IDCODE);
  bsp_printf("REV_ID: 0x%X\r\nDEV_ID: 0x%X\n", DBGMCU->IDCODE >> 16,
                                            DBGMCU->IDCODE & 0xFFF);

  // initialize drivers this board supports
  bsp_i2c_init();
  bsp_printf("I2C initialized\n");

  bsp_spi_init();
  bsp_printf("SPI initialized\n");

  init_devices();
  bsp_printf("initialized devices\n");

/*
  // these should be configured more elegantly like how the i2c stuff is configured
  // ADC inputs
  palSetPadMode(GPIOB, 1, PAL_MODE_INPUT_ANALOG); // PB1, ADC channel 5
  palSetPadMode(GPIOA, 3, PAL_MODE_INPUT_ANALOG); // PA3, ADC channel 15
  palSetPadMode(GPIOC, 0, PAL_MODE_INPUT_ANALOG); // PC0, ADC channel 10
  palSetPadMode(GPIOC, 3, PAL_MODE_INPUT_ANALOG); // PC3, ADC channel 13

  // PWM on PE11, timer 1 channel 2?
  palSetPadMode(GPIOE, 11, PAL_MODE_ALTERNATE(1));
*/

  heartbeat_start();
  bsp_printf("heartbeat thread started\n");

  bsp_printf("End of BSP init\n\r\n");
}

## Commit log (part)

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2025-06-11 first commit. some UART RTL, readme, etc
2025-06-11 update plans
2025-06-12 updating the gameplane
2025-06-13 update the plan
2025-06-13 readme for modules
2025-06-13 mapping out file structure
2025-06-13 top comment
2025-06-13 more of it
2025-06-13 add mkupdater rough plan file
2025-06-13 attributes
2025-06-13 update readme and structure
2025-06-13 updating readme
2025-06-14 trying to get DAC example working
2025-06-14 vendor import
2025-06-14 need to debug DAC. no audio, only clicks. at least get it from both headphones
2025-06-14 this creates sound on the DAC pins
2025-06-14 this makes sound...
2025-06-14 gitignore
2025-06-14 cleanup build dir
2025-06-15 this seems to change pitch but not that great sounding. attempting sample rate at 44.1khz
2025-06-15 more gitignore
2025-06-15 sounds like multi voice
2025-06-15 sounds a bit better
2025-06-15 trying interrupts but nothing it working!!!
2025-06-15 this appears to do something
2025-06-15 chibi semaphore example that seems to work decent. bit of noise tho on the circuit it seems
2025-06-15 some good working interrupt stuff using GPIO loopback
2025-06-16 i had a sine wave from the testhal example working but not with a dynamically generated sine wave!
2025-06-16 SCB_CleanDCache_by_Addr fixed this????
2025-06-16 getting the hang of GPT timers
2025-06-17 for gdb server bringup
2025-06-17 remove comments
2025-06-17 move around some stuff
2025-06-17 monitor doesnt work but spawning, listing, killing does
2025-06-17 cleanup
2025-06-17 chibios submodule. change aam makefile
2025-06-18 fighting the build
2025-06-19 no cmake here. lets stick with what chibios is providing and go from there
2025-06-19 schematic updates
2025-06-20 update schematic and pcb. errors
2025-06-21 more schematic updates. semiworking PCB
2025-06-22 attempt at FMC interface
2025-06-23 display driver schematic piece
2025-06-23 updating FMC pins
2025-06-24 UUM SPI flash. gpio ctrl with 74lvc
2025-06-24 add CAN tranceivers
2025-06-24 CAN rework
2025-06-24 PCB updates
2025-06-24 PCB update. CAN routing. making space. may need 4 layers!
2025-06-25 attempting CAN routing. semi routed pcb
2025-06-25 all connections appear valid. some silkscreen clipping
2025-06-25 my CAN trscvr LAYOUT sucks
2025-06-25 CAN pos neg lines routed. broke other shit. autoroute hates me
2025-06-26 routed no errors
2025-06-27 progress. might have enough of the vital stuff routed to get the autorouter working for the rest. not sure if it will follow rules though
2025-06-27 a bit of auto routing based on the literal stub traces I put in
2025-06-27 ugh routing is a bit messy right now. need to go back to schematic and finish up wiring i forgot about primarily the UARTs for debugging on all boards and the cmd UART from AAM<->ACM
2025-06-28 good progress. build from here. bit of autorouter. not too shitty
2025-06-28 i sort of like this. verifying one more time before printing
2025-06-28 adding JLCPCB files
2025-06-29 adding v2 schematic. working with USB
2025-06-29 i should really make this multiple sheets
2025-06-29 removing the courtyard from the filler plots. theyre not actually components just an outline with throughholes
2025-06-29 moving to multiple sheets for the schematic
2025-06-29 should probably write some code now
2025-06-30 adding more sheets in the schematic
2025-07-03 progress on putting things in different sheets
2025-07-04 v2 updates. remove sniffer
2025-07-04 moving AAM -> APM. creatint some abstraction like stuff
2025-07-05 no errors in the ERC!
2025-07-05 need to update PCB and new traces
2025-07-05 attempting new PCB layout
2025-07-06 time to start routing?
2025-07-07 gonna throw auto route on. I think I have enough put together for now
2025-07-07 schematic updates, no errors at least. running DRC on pcb
2025-07-07 fixed designators
2025-07-07 routed with no errors. could probably do some more verification before sending the initial order of the v2 revamp then start designing out the AFFM module
2025-07-09 routed. saving the extra board in the same pcb file for when I want to creat the filter and fx module
2025-07-12 attempting v2 spinout with jlcpcb
2025-07-16 hmmm figuring out filter module right now
2025-07-17 need to learn more about variable lpf, wiring, minimal capacitor for the circuit and cutoff with series resistor
2025-07-19 schematic updates for affm
2025-07-20 working on the new framework16
2025-07-20 backups
2025-07-21 hmmm lpf, hpf, bpf, bsf all in there. I could probably make the board much smaller...
2025-07-21 dip switch for multi pole filter? this is all for experimenting for now, a refined design with less togleables will come later
2025-07-21 dip switch symbol. how might this work...
2025-07-22 cool LPFs. i want to add some toggleability between my RC passive and active implementations...
2025-07-27 some progress on affm board
2025-07-30 now making a v3 with HATs for each nucleo with my needed shit. this will make things very compact and hopefully much cheaper
2025-07-30 moving to github.com/akielaries/signalmesh_CAD
2025-08-31 clock speed should be higher
2025-08-31 i was using a bad freuqency bc of the prescaler computation on the chibi ll gpt driver
2025-09-01 reset
2025-09-01 remove stuff
2025-09-01 revert chibios stuff
2025-09-01 increase gpt6 frequency to 75mhz
2025-09-01 attempting some adc conversion stuff
2025-09-02 such a pain getting a second measurement. how did i do it earlier?
2025-09-06 working 3 channel ADC example
2025-09-06 remove some "tools"
2025-09-06 format
2025-09-06 idk how accurate this internal temperature reading im doing actually is
2025-09-06 weird internal temp values...?
2025-09-06 removes?
2025-09-06 no clue whats wrong with internal temp reading
2025-09-07 reading 4 channels. attempting other 2 in another conversion group
2025-09-07 i think i did this right. v_sense and v_ref reading correctly? 3v3 and about 86 deg C for v_sense
2025-09-08 debugging the shit out of cmake. i like the simplified version better
2025-09-08 remove most of the cmake experiment
2025-09-08 attempting my own toolchainification?
2025-09-09 cmake-ifying chibi myself
2025-09-09 works good enough tbh. wheni want to use this for the f4, f1, etc. i can cross reference stuff
2025-09-28 working on waveform shit
2025-09-28 saw, triangle, and square wave generators
2025-09-28 works pretty well
2025-10-19 add the pwm driver
2025-10-19 trying pwm driver with mg996r servo
2025-10-19 trying again. not working great
2025-10-20 working pwm. not working on the servo tho
2025-10-20 servo code does something. the top claw on the arm is too tight, not enough torque on the thing but maybe it needs more power...?
2025-10-20 a hack but it works
2025-11-30 updates to the servo driver
2025-12-03 attempting bsp stuff
2025-12-05 cxx options cmake
2025-12-05 idk how this actually works rn
2025-12-06 seeing some structure now. need to cleanup some cmake files
2025-12-07 aha more success?
2025-12-07 more updates. same clock?
2025-12-08 trying more stuff
2025-12-08 diagnosing i2c failures. i can only imagine the pain this will be for SPI and CAN...
2025-12-08 working xmit?
2025-12-10 attempting i2c scan?
2025-12-10 found both i2c devices
2025-12-12 getting there
2025-12-13 attempt at some linux like driver abstraction but not really
2025-12-13 formatting. using bme280 driver works
2025-12-13 more progress. script using linker defs for mem usage
2025-12-13 more progress. got a cool driver abstraction going. linux mnakes it a lil more sophisticated
2025-12-14 moving on. configuring oversampling
2025-12-14 idk how accurate these readings really are
2025-12-14 accurate?
2025-12-14 conversions
2025-12-14 compiles, seems to work. bme readings seem accurate
2025-12-14 gonna move away for4m str usage next
2025-12-14 units and formatting some things
2025-12-14 works decent. needs some better abstraction
2025-12-15 not quite what i want but some progress
2025-12-15 comment
2025-12-17 inlining funcs
2025-12-17 global device struct
2025-12-17 no more heap alloc
2025-12-19 linking updates. formatting
2025-12-20 i think this works
2025-12-20 rearrange
2025-12-20 starting on ina3221 driver
2025-12-20 bh1750 sensor. no idea if it works. could test on arduino
2025-12-20 aht2x temp/hum driver
2025-12-21 tricky spiflash driver. hanging after acquire and attempting to send cmd
2025-12-22 hmmm
2025-12-30 shitty spi loopback that doesnt work...
2026-01-01 attempting spi loopback
2026-01-01 i guess the GPIO speed matters for the logic analyzer? smells problematic
2026-01-02 working on common stuff now too
2026-01-02 attempting w25 flash test again. need to read manual again...
2026-01-02 working. spiExchange assumed same size for tx and rxbuf?
2026-01-02 sticking with exchange
2026-01-03 attempting reset
2026-01-03 issues with status read?
2026-01-04 broken
2026-01-04 broken broken
2026-01-05 working read back!
2026-01-06 upping the SPI divisor
2026-01-06 upping speed more
2026-01-08 gpio G0 doesnt work for my test?
2026-01-08 idk if this will really work for spi?
2026-01-09 i guess it does work. running at 888kb/s
2026-01-09 working fast?
2026-01-10 getting the display drivers working. got some font stuff working as a 5x7
2026-01-10 somewhat working
2026-01-12 adding lcd 20x04 driver and more bist stuff
2026-01-17 some driver and APM updates
2026-01-17 update ACM RTL. need to change the name and figure out pin assignments for things
2026-01-17 restructuring pin defs, starting with the old blinky
2026-01-17 alias?
2026-01-17 add fpga server
2026-01-17 afm updates
2026-01-17 loader works??!
2026-01-18 comments
2026-01-18 more RTL for clock stuff
2026-01-19 rem artifacts
2026-01-19 gitignore updates
2026-01-19 fumbling with a PLL
2026-01-19 working PLL with 132mhz output
2026-01-19 running at 248mhz
2026-01-20 attempting a proper project for this
2026-01-20 both PLLs but the second signal for 250mhz is still very noisy. maybe i'm doing it wrong
2026-01-21 working on reading external frequencies from the FPGA into the STM32H755 using the divided clock. working on my own parallel bus interface
2026-01-22 attempting some uart stuff
2026-01-22 uart example working? idk
2026-01-25 using gowin ide and some other stuff
2026-01-25 gitignore update
2026-01-25 trying to create a top module
2026-01-25 as close to working as ive gotten it so far for UART
2026-01-31 remove build files?
2026-02-23 readme
2026-02-28 ddr3 getting there
2026-03-01 toggle fpga power using a pi gpio
2026-03-01 fpgapwr update
2026-03-04 builds. need to test
2026-04-11 ide stuff i think
2026-04-11 readme update
2026-06-14 memory mapped qspi working with dual lane support
2026-06-14 new memmap stuff
2026-06-18 adding in ACM FPGA project. got QSPI memap dual lane mode working well on APM
2026-06-18 infra for boot. what next?
2026-06-19 FPGA -> STM32H755 UART working
2026-06-19 add in ll UART driver. working DMA based FPGA->STM32 UART at 1mbaud
2026-06-19 trying to get the FMC working between FPGA and STM32H753. not much luck yet
2026-06-20 stm FMC clock issue maybe? can see LEDs blink in memapped mode with gdb but not FW
2026-06-20 8 BIT DATA MEM MAP WORKS!
2026-06-20 trying 16 bit data again
2026-06-20 does STM32_FMCSEL_PER_CK work better than STM32_FMCSEL_HCLK?
2026-06-25 new FPGA targets. update the W25QXX SPIFLASH driver and memory map examples. new 128MBIT IC in the mix but qspi quad lane doesnt work
2026-06-27 trying to get USB driver working
2026-06-27 USB enumeration working but required some hacks in the chibi project. maybe worth upstreaming
2026-06-27 lots of working stuff mostly cheby and FMC + wishbone 16 bit bus related. ran into weird regression that is actually a flaky wiring issue on my end
2026-06-28 more good stuff finally. polyphony seems to work up to 8 voices. doesnt sound that great
2026-06-28 arch diagram
2026-06-28 working on docs, polyphony, and general cleanup. bunch of random test files. need structure!
